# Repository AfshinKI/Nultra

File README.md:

# Nultra

Nultra is a Bluetooth LE wall switch designed for switch boxes without a neutral wire. One AA cell powers the control electronics. A faceplate button or the nearby iPhone and Android apps can operate the latching relay.

[Open the enclosure document in Onshape](https://cad.onshape.com/documents/3cb2e23a19093c4389ce2f07/w/3be343cdcd1e5951d1a37be1)

## Build and use a switch

| What you want to do | Where to start |
| --- | --- |
| Inspect, adapt or print the enclosure | [Mechanical design, STEP solids and printable STL files](hardware/mechanical/) |
| Study the circuit or inspect the original v2 manufacturing outputs | [Electronics, KiCad review findings and archived fabrication files](hardware/README.md#electronics) |
| Build firmware for the STM32WB05KZ and provision a switch | [Firmware build and pairing](firmware/README.md) |
| Control a switch from a phone | [iOS and Android setup](app/README.md) |

Start with the firmware guide when building a new unit. It generates a separate pairing PIN and command password for each switch. Keep the generated header and firmware image private. Owners upgrading older devices should provision fresh credentials, clear old Bluetooth bonds and pair their controllers again.

The KiCad project is an editable conversion with outstanding connectivity findings. For example, the archived v2 board assigns the positive battery contact to `VBATT`, but the corresponding numbered pad is missing in the conversion. Check the archived fabrication files before ordering a changed board. The STEP and STL files can be opened independently of SolidWorks. [Hardware notes](hardware/README.md)

## Project site

The 3D demo opens the Nultra iPhone app and taps Desk Lamp to light the room. On a fresh visit, the camera approaches the mounted switch. Three pairs of magnets release as the faceplate lifts away. The switch stays secured by two screws while a callout identifies the AA cell and shows its discharge profile. Then the screws back out, the uncovered switch comes forward, and the AA cell lifts out before the carrier, board and shell separate. [Interactive room renderer](docs/room.js) · [Path-traced teardown renderer](tools/render_wall_teardown.py) · [Room artwork and prompts](tools/room_artwork.md)

The camera identifies the printed antenna, Bluetooth CPU and SWD debug pads on the front of the PCB. It slows on the reverse to show the DC/DC converter, latching relay and AC load terminal. After one full tour, the callouts clear, the sequence rewinds to the room and the opening lamp demo loops. Scrolling takes over at the current view. The chapter buttons and slider also work with reduced motion. Replay tour starts the sequence again, using stills when reduced motion is enabled. Each demonstration below the tour has its own replay control for the tactile button, battery indicator, cell replacement or companion app. [Render script](tools/render_product.py) · [AA model preparation](tools/prepare_render_battery.py)

J5 carries SWDIO and SWCLK. U1 is the STM32WB05KZ Bluetooth MCU. On the opposite side, U4 is the TPS613221A boost converter and R5 is the Panasonic AGQ21TA2H latching relay. [V2 pad connections](hardware/electronics/fabrication/v2/Nultra-v2-pad-connections.csv) · [V2 bill of materials](hardware/electronics/fabrication/v2/Nultra-v2-BOM.csv)

The AA discharge graph uses the firmware’s voltage-to-charge lookup table, from 1.65 V at 100% to 0.65 V at 0%. The firmware requests a 2 ms pulse to change the latching relay, then disables the drive. The relay holds its position with its coil unpowered. The controller can sleep between radio events. [Battery estimate](firmware/BLE_Peripheral_Lite/Core/Src/main.c#L702) · [Relay drive](firmware/BLE_Peripheral_Lite/Core/Src/main.c#L887) · [Controller sleep](firmware/BLE_Peripheral_Lite/Core/Src/app_entry.c#L310)

The close-up in the build-files section was path traced from the Altium board and the positioned AA cell using a thin-lens camera focused on the microcontroller. [Board photograph renderer](tools/render_board_detail.py)

To preview the site locally, run `python -m http.server --bind 127.0.0.1 --directory docs 8000` from the repository root.

## Development history

Firmware development began in March 2025. The public archive preserves the original commit dates and merges. Device credentials and compiled firmware images were omitted from those revisions. [Browse the 2025 firmware commits](https://github.com/AfshinKI/Nultra/commits/d4c3cc2b9a1dbfadcdf72ec14c10238a79e72ddd/)

The September 2026 mobile app commits follow the iPhone and Android controllers through Bluetooth pairing, scenes and home-screen widgets. These archived revisions omit shared credentials and private distribution files. [Browse the mobile app commits](https://github.com/AfshinKI/Nultra/commits/8fd76693fbb15d21747a63de8b6250752ec708d2/)

## Licenses

The original Nultra hardware uses CERN-OHL-P-2.0. Original software and documentation use MIT. The ST-derived firmware files retain ST’s SLA0044 terms, including its ST-hardware restriction. The license notice identifies those files and other third-party materials. [License scope and notices](LICENSE)

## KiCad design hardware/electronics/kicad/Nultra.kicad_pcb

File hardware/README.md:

# Nultra hardware

| To work on | Start here |
| --- | --- |
| Enclosure fit or assembly | [Single-switch STEP](mechanical/assemblies/single-switch.step) or [double-switch STEP](mechanical/assemblies/double-switch.step) |
| An individual machined or printed part | [STEP solids](mechanical/step/) and [print meshes](mechanical/prints/) |
| The circuit and PCB layout | [KiCad 10 project](electronics/kicad/Nultra.kicad_pro) |
| The original v2 fabrication run | [Gerbers, drills, BOM and pad connections](electronics/fabrication/v2/) |

## Enclosure

The STEP assemblies use millimetres and preserve the saved positions of the single and double switch designs. The single model contains the faceplate, wordmark, carrier, rear shell and bare PCB. The double model has one wide faceplate, one wordmark and two sets of the other parts. Their outside dimensions are approximately 70 × 115 × 31 mm and 116 × 115 × 31 mm. Each assembly imports as named components in a STEP-capable CAD application. The CAD export contains solid geometry and assembly placements. Parametric sketches and mechanical mates are unavailable in this exchange format.

Open a faceplate and its matching wordmark STL together as a multipart object to keep their shared print coordinates. Use one carrier and one rear shell per switch mechanism. The [v2 bare-board STEP](electronics/cad/bare-board-v2.step) preserves the board outline and holes from the original electronics export. The assembly models omit purchased components such as the cell, light pipe and board-mounted devices, so their clearances require separate review.

The five individual STEP files come from the enclosure part geometry. The assemblies use the saved component transforms from the original housing design. Every exported body passed an Open Cascade solid-validity check after reimport, including the six individual letters. The six STL triangle payloads match the original print exports.

## Electronics

Open the KiCad project from its own folder to resolve the local symbol and footprint libraries. The editable schematic and two-layer board come from the later Altium working files. The board has 50 placed footprints and the local library contains its 29 distinct land patterns.

**Use the KiCad project as an editing baseline.** KiCad 10.0.4 reported 10 schematic errors and 12 warnings. The board check reported 1,083 rule violations, one unconnected item and 152 schematic-to-board findings. These include apparent shorts, a missing ground connection and conflicting pin or net names. Compare any newly generated artwork with the v2 Gerbers and resolve electrical connectivity before making a changed board.

### Archived v2 production data

The manufacturing ZIP preserves the original layer and drill payloads from January 1, 2025. Top and bottom copper use `.GTL` and `.GBL`, solder mask uses `.GTS` and `.GBS`, silkscreen uses `.GTO` and `.GBO`, and solder paste uses `.GTP` and `.GBP`. The board outline is `.GM` and the keep-out drawing is `.GKO`. Include both the round-hole and slot Excellon files when viewing the job.

The BOM came from the same v2 fabrication folder. The pad connection table lists reference, pad number and board net for 155 distinct combinations across 36 named nets. It was extracted from the PCB saved 43 seconds before the archived Gerber report. Only named pads appear in the table. An empty net field means the board assigned no net. The antenna carries the original placeholder reference `*`. The archive contains no v2 pick-and-place file.

The editable schematic and PCB have later modification dates. For example, the historical board assigns battery contact BT1 pad `+` to `VBATT`, while the KiCad board lacks that numbered pad. U1 pins 25 and 27 also carry different net names between the two files. Use the archived pad table to check these differences alongside the artwork.

## Hardware notices

Original Nultra enclosure geometry, circuit design and board layout are released under [CERN-OHL-P-2.0](../LICENSES/CERN-OHL-P-2.0.txt). The project symbol and footprint libraries contain the component definitions used in this design. The Altium schematic identifies the author's component libraries and the Altium Content Vault as sources. Third-party component definitions retain their applicable terms.

The Keystone Electronics 5223 battery contact, BT1, includes SnapEDA sourcing metadata. Its symbol and footprint were converted to KiCad format. SnapMagic Search describes its individual component files as CC BY-SA 4.0 with Design Exception 1.0. The exception covers their use within a board design. [5223 part page](https://www.snapeda.com/parts/5223/Keystone/view-part/) · [SnapMagic license and design exception](https://www.snapeda.com/about/terms/) · [CC BY-SA 4.0](https://creativecommons.org/licenses/by-sa/4.0/)

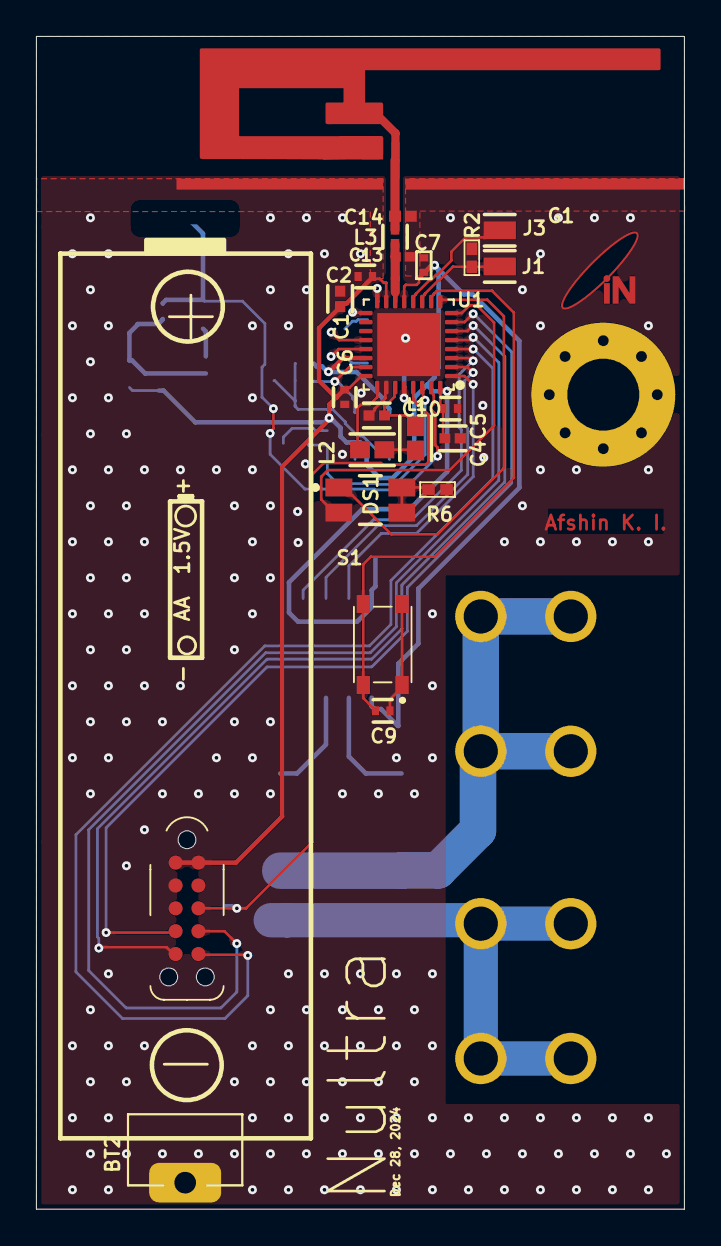
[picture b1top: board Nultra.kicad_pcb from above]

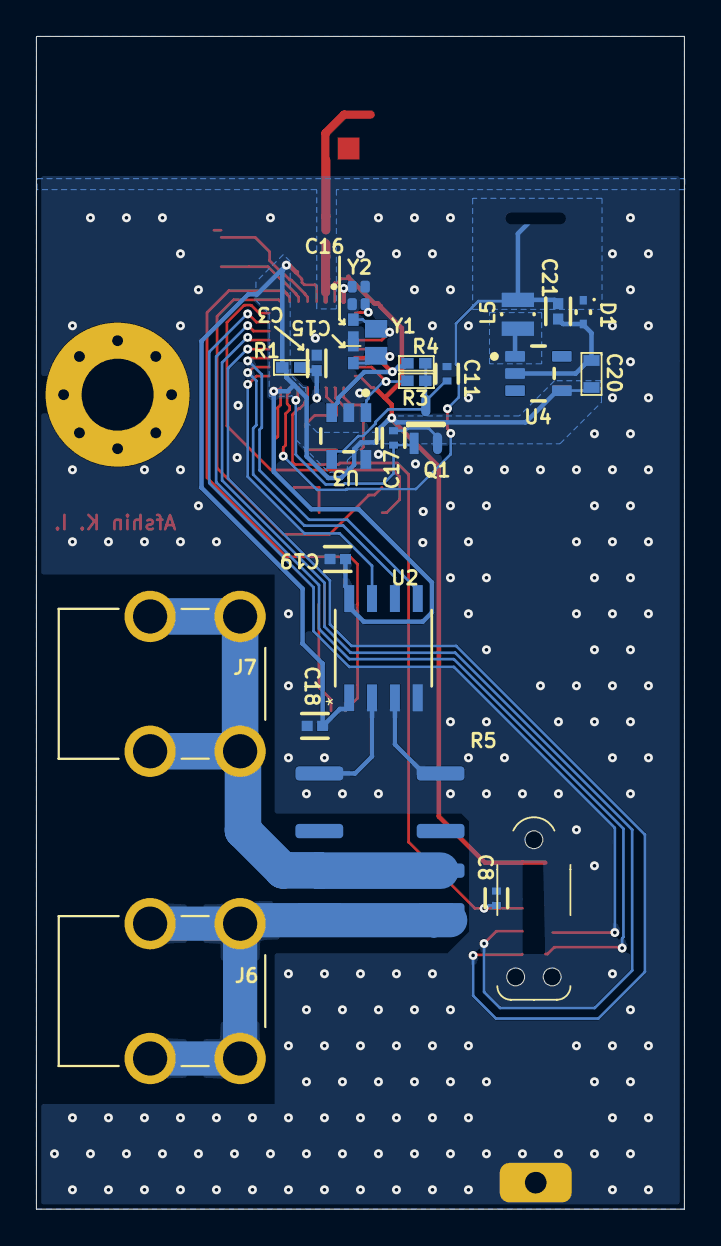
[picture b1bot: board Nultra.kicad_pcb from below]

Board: 2 copper layers, 36.0 x 65.2 mm, 50 parts (24 on the bottom side), 36 nets.

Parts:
AE1: IFA_2.4GHz; IFA_CC2430DB
BT1: 5223; 5223_battery_AA
BT2: 1017-1; BAT_1017-1
C1, C3, C4, C10, C18, C19, C21: GRM155R60J475ME47D; FP-GRM155-0_1-IPC_B
C2, C5, C6, C7, C8, C9, C11, C17: GRM155R71C104KA88D; FP-GRM15-MFG
C13: GRM1555C1HR80BA01D; CAPC1005X55X25LL05T10
C14: GRM1555C1HR30BA01D; CAPC1005X55X25NL05T10
C15, C16: GRM1555C1H100JA01D; C0402
C20: CL10A226MP8NUNE; C0603
D1: ESD5Z3.3T1G; ONSC-SOD-523-2-502-01_V
DS1: LTST-C155GEKT; LTST-C155GEKT_V
G1: InoTable; INNOVETRON_2s
J1, J3: S2761-46R; FP-S2761-46R-MFG
J5: InoSD; InoSD_single_q
J6, J7: 8190; KEYSTONE_8190
L1, L2: LQM18DN100M70L; FP-LQM18DN_70-IPC_B
L3: LQG15HS2N7S02D; FP-LQG15HH_02-IPC_C
L5: 1286AS-H-2R2M=P2; FP-DFE201612C-MFG
M1: mountHole_4M; MountHole_4M
Q1: BSS209PWH6327XTSA1; FP-PG-SOT323-3-IPC_A
R1: DNP; R0402
R2, R3, R4: RC0402JR-074K7L; R0402
R5: AGQ21TA2H
R6: RC0402FR-071KL; R0402
S1: TL3365AF180QG
U1: STM32WB05KZV6TR; VFQFPN32
U2: TPM8837C-SO1R; SOP-8_TPK
U3: AT24C01D-STUM-T; FP-C04-21344-MFG
U4: TPS613221ADBVR; FP-DBV0005A-MFG
Y1: STDMUB1-32.768K; XTAL_NX2012SA_NDK
Y2: 416F32022CKR; XTAL_416F32022CKR

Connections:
Button: C9.2, S1.3, S1.4, U1.10
GND: AE1.GND, BT2.-, C1.2, C2.1, C3.2, C4.2, C5.1, C6.1, C7.1, C8.1, C9.1, C10.2, C11.2, C13.1, C14.1, C15.1, C16.1, C18.1, C19.1, C20.1, C21.2, D1.2, J5.2, R2.1, R6.1, S1.1, S1.2, U1.26, U1.33, U2.4, U3.2, U3.5, U4.2, Y2.2, Y2.4
HSE_X1: U1.17, Y2.3
HSE_X2: U1.16, Y2.1
LSE_X1: C15.2, U1.21, Y1.1
LSE_X2: C16.2, U1.20, Y1.2
Net*_ANT: AE1.ANT, C14.2, L3.2
NetC10_1: C10.1, L1.1, U1.27
NetC11_1: C11.1, Q1.3, R3.2, R4.2, U3.4
NetC13_2: C13.2, L3.1, U1.14
NetDS1_3: DS1.3, DS1.4, R6.2
NetJ6_1: J6.1, R5.4, R5.5
NetJ7_1: J7.1, R5.3, R5.6
NetL1_2: L1.2, L2.1
NetL2_2: L2.2, U1.25
NetL5_1: L5.1, U4.1
NetR5_1: R5.1, U2.2
NetR5_8: R5.8, U2.3
RF_RX: J3.1, U1.12
RF_TX: J1.1, R2.2, U1.11
RSTN: C8.2, J5.8, U1.29
SCL: R3.1, U1.23, U3.1
SDA: R4.1, U1.22, U3.3
SWCLK: J5.7, U1.5
SWDIO: J5.5, U1.6
UART_RX: J5.6, U1.4
UART_TX: J5.4, U1.7
VBATT: C21.1, D1.1, L5.2, U1.31
VCAP: C3.1, R1.2, U1.28
VCC: C1.1, C2.2, C4.1, C5.2, C6.2, C7.2, C17.2, C18.2, C19.2, C20.2, J5.1, J5.10, Q1.2, R1.1, U1.13, U1.15, U1.24, U1.32, U2.1, U2.8, U4.4
ee_en: C17.1, Q1.1, U1.30
ee_en_g: DS1.1, U1.9
ee_en_r: DS1.2, U1.8
relay_en: U1.1, U2.7
relay_reset: U1.3, U2.5
relay_set: U1.2, U2.6

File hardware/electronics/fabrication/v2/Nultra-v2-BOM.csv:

Comment,Description,Designator,Footprint,LibRef,Quantity

"IFA_2.4GHz","","","IFA_CC2430DB","IFA_2.4GHz","1"
"InoTable","","","INNOVETRON_2s","InoTable","1"
"5223","AA battery +","BT1","5223_battery_AA","5223","1"
"1017-1","Batt AA -","BT2","BAT_1017-1","1017-1","1"
"GRM155R60J475ME47D","Chip Multilayer Ceramic Capacitors for General Purpose, 0402, 4.7uF, X5R, 15%, 20%, 6.3V","C1, C3, C4, C10, C18, C19, C21","FP-GRM155-0_1-IPC_B","CMP-2008-04549-2","7"
"GRM155R71C104KA88D","CAP CER 0.1UF 16V X7R 0402","C2, C5, C6, C7, C8, C9, C11, C17","FP-GRM15-MFG","CMP-2100-03641-2","8"
"GRM1555C1HR80BA01D","","C13","CAPC1005X55X25LL05T10","CMP-1034-00043-2","1"
"GRM1555C1HR30BA01D","","C14","CAPC1005X55X25NL05T10","CMP-1034-00009-2","1"
"GRM1555C1H100JA01D","10pF","C15, C16","C0402","Cap_S","2"
"CL10A226MP8NUNE","CAP CER 22UF 10V X5R 0603","C20","C0603","Cap_S","1"
"ESD5Z3.3T1G","Transient Voltage Suppressor, Micro-Packaged Diode for ESD Protection, 2-Pin SOD-523, Pb-Free, Tape and Reel","D1","ONSC-SOD-523-2-502-01_V","CMP-1063-00098-1","1"
"LTST-C155GEKT","LED Bi-Color Green / Red, 100 mW, 30 mA, -55 to 85 degC, 4-Pin SMD, RoHS, Tape and Reel","DS1","LTST-C155GEKT_V","CMP-2000-06619-1","1"
"S2761-46R","PC TEST POINT NATURAL","J1, J3","FP-S2761-46R-MFG","CMP-15817-000011-1","2"
"InoSD","Cbl Plug-Of-Nails 10-Pin w/Legs","J5","InoSD_single_q","InoSD","1"
"8190","4 Pin Screw Terminal, Power Tap 6-32 Through Hole, Right Angle","J6, J7","KEYSTONE_8190","8190","2"
"LQM18DN100M70L","Multilayer type Inductor for Power Lines 10uH ±20% @1MHz, 300mA, Max DCR 1.365O, SRF 32MHz","L1, L2","FP-LQM18DN_70-IPC_B","CMP-06042-017052-1","2"
"LQG15HS2N7S02D","Multilayer type RF Inductor 2.7nH ±0.3nH 0.12O 800mA 0402","L3","FP-LQG15HH_02-IPC_C","CMP-2000-06580-2","1"
"1286AS-H-2R2M=P2","Shielded Wirewound Inductor 2.2uH 20% 1300mA 0.192O 0806 (2016)","L5","FP-DFE201612C-MFG","CMP-06042-011489-1","1"
"mountHole_4M","","M1","MountHole_4M","mountHole_4M","1"
"BSS209PWH6327XTSA1","MOSFET P-CH 20V 630MA SOT323-3","Q1","FP-PG-SOT323-3-IPC_A","CMP-32901-000806-1","1"
"DNP","Generic Resistor","R1","R0402","Res_Cube","1"
"RC0402JR-074K7L","4.7K","R2, R3, R4","R0402","Res_Cube","3"
"AGQ21TA2H","","R5","AGQ21TA2H","AGQ21TA2H","1"
"RC0402FR-071KL","1K","R6","R0402","Res_Cube","1"
"TL3365AF180QG","BTN","S1","TL3365AF180QG","TL3365AF180QG","1"
"STM32WB05KZV6TR","IC RF TxRx + MCU Bluetooth Bluetooth v5.4 32-VFQFN Exposed Pad","U1","VFQFPN32","STM32WB05KZV6TR","1"
"TPM8837C-SO1R","No Description Available","U2","SOP-8_TPK","TPM8837C-SO1R","1"
"AT24C01D-STUM-T","IC EEPROM 1KBIT I2C 1MHZ SOT23-5","U3","FP-C04-21344-MFG","CMP-06313-000152-1","1"
"TPS613221ADBVR","IC REG BOOST 3.3V 1.6A SOT23-5","U4","FP-DBV0005A-MFG","CMP-04918-000080-1","1"
"STDMUB1-32.768K","No Description AvailableDigiKey : 644-STDMUB1-32.768KCT-ND","Y1","XTAL_NX2012SA_NDK","STDMUB1-32.768K","1"
"416F32022CKR","","Y2","XTAL_416F32022CKR","416F32022CKR","1"

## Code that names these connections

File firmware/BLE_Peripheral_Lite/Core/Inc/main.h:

/* USER CODE BEGIN Header */
/**
  ******************************************************************************
  * @file           : main.h
  * @brief          : Header for main.c file.
  *                   This file contains the common defines of the application.
  ******************************************************************************
  * @attention
  *
  * Copyright (c) 2024 STMicroelectronics.
  * All rights reserved.
  *
  * This software is licensed under terms that can be found in the LICENSE file
  * in the root directory of this software component.
  * If no LICENSE file comes with this software, it is provided AS-IS.
  *
  ******************************************************************************
  */
/* USER CODE END Header */

/* Define to prevent recursive inclusion -------------------------------------*/
#ifndef __MAIN_H
#define __MAIN_H

#ifdef __cplusplus
extern "C" {
#endif

/* Includes ------------------------------------------------------------------*/
#include "stm32wb0x_hal.h"
#include "app_entry.h"
#include "app_common.h"
#include "app_debug.h"
#include "compiler.h"

/* Private includes ----------------------------------------------------------*/
/* USER CODE BEGIN Includes */
#include "stm32wb0x_nucleo.h"
/* USER CODE END Includes */

/* Exported types ------------------------------------------------------------*/
/* USER CODE BEGIN ET */

/* USER CODE END ET */

/* Exported constants --------------------------------------------------------*/
/* USER CODE BEGIN EC */
#define PASSWORD_SIZE 8
extern volatile bool relay_status;
extern volatile uint64_t serial_num;
void Timer16_Callback(void);
HAL_StatusTypeDef EEPROM_WriteSerialNumber(uint64_t serial);
/* USER CODE END EC */

/* Exported macro ------------------------------------------------------------*/
/* USER CODE BEGIN EM */

/* USER CODE END EM */

/* Exported functions prototypes ---------------------------------------------*/
void Error_Handler(void);

/* USER CODE BEGIN EFP */

/* USER CODE END EFP */

/* Private defines -----------------------------------------------------------*/
#define relay_en_Pin GPIO_PIN_3
#define relay_en_GPIO_Port GPIOB
#define relay_set_Pin GPIO_PIN_2
#define relay_set_GPIO_Port GPIOB
#define relay_reset_Pin GPIO_PIN_1
#define relay_reset_GPIO_Port GPIOB
#define led_r_Pin GPIO_PIN_0
#define led_r_GPIO_Port GPIOA
#define led_g_Pin GPIO_PIN_8
#define led_g_GPIO_Port GPIOA
#define button_Pin GPIO_PIN_9
#define button_GPIO_Port GPIOA
#define ee_en_Pin GPIO_PIN_5
#define ee_en_GPIO_Port GPIOB

/* USER CODE BEGIN Private defines */


/* USER CODE END Private defines */

#ifdef __cplusplus
}
#endif

#endif /* __MAIN_H */

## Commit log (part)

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2025-03-13 project files
2025-03-15 long for reset
2025-03-15 verion added to the name
2025-03-15 name issue fixed
2025-03-18 WDT set to overflow at ~93ms
2025-03-23 oraange color and init name added
2025-03-27 if fixed with ==
2025-03-29 name has extra information, state and battery
2025-09-13 new percentage formula added
2025-09-14 read me updated
